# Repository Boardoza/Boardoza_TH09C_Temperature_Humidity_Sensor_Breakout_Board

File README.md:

# Boardoza TH09C Temperature Humidity Sensor Breakout Board
The TH09C Digital Temperature and Humidity Sensor Breakout Board offers reliable environmental monitoring with high accuracy and low power consumption. Featuring the TH09C sensor, this board provides precise digital temperature and humidity readings via an I<sup>2</sup>C interface. Its fast response time and high repeatability make it ideal for use in HVAC systems, weather stations, and other applications where environmental data is critical. 

### [Click here to purchase!](https://www.ozdisan.com/maker-and-iot-products/boardoza/boardoza-modules/BOARDOZA-TH09C/1206510)

|Front Side|Back Side|
|:---:|:---:|
| | |

---
## Key Features
- Ultra-Accurate Sensing: Temperature sensor with ±0.15°C accuracy and relative humidity sensor with typical ±2.0%RH accuracy.
- Wide Sensing Range: Supports temperature measurement from –40°C to 100°C and humidity from 0% to 100%.
- Digital Output: Provides digital temperature and humidity readings via TTL I2C interface for easy integration.
- Low Power Consumption: Optimized for battery-operated devices with minimal energy usage.
-Compact Design: Small form factor suitable for a wide range of environmental monitoring applications.

---

## Technical Specifications

**Input Voltage:**	2V - 5.5V

**Voltage Input Type:**	Molex 4 pin 2.50mm header

**Interface:** I<sup>2</sup>C  

**Functions:**	Temprature and Humidity Sensor

**Temperature Accuracy:** ±0.15°C  

**Humidity Accuracy:** Typical ±2.0% RH  

**Measurement Range:**	 -40°C ~ +100°C

**Operating Humidity:** 0% to 100% RH  

**Operating Temperature:**	-40°C ~ +100°C

**Board Dimensions:**	20mm x 20mm

---
## Board Pinout
| (J1) Pin Number | Pin Name | Description |
|:---:|:---:| --- |
| 1 | VCC | Power Supply |
| 2 | SCL | I<sup>2</sup>C Serial Clock Pin |
| 3 | SDA | I<sup>2</sup>C Serial Data Pin|
| 4 | GND | Ground|

---
## Board Dimensions

---
## Step Files

[Boardoza TH09C.step]( ./assets/TH09C%20Step.step)

---
## Datasheet

[Boardoza TH09C Datasheet.pdf](./assets/TH09C%20Datasheet.pdf)

---
## Version History
- V1.0.0 - Initial Release

---
## Support
- If you have any questions or need support, please contact support@boardoza.com

---
## License

Shield: [![CC BY-SA 4.0][cc-by-sa-shield]][cc-by-sa]

This work is licensed under a [Creative Commons Attribution-ShareAlike 4.0 International License][cc-by-sa].

[![CC BY-SA 4.0][cc-by-sa-image]][cc-by-sa]

[cc-by-sa]: http://creativecommons.org/licenses/by-sa/4.0/
[cc-by-sa-image]: https://licensebuttons.net/l/by-sa/4.0/88x31.png
[cc-by-sa-shield]: https://img.shields.io/badge/License-CC%20BY--SA%204.0-lightgrey.svg

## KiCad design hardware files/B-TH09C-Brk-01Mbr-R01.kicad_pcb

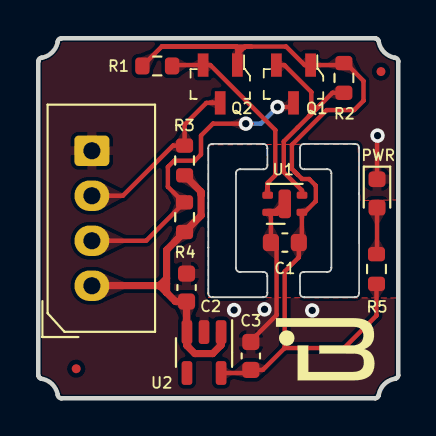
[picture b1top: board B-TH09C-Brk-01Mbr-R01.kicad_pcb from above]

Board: 2 copper layers, 20.0 x 20.0 mm, 14 parts (0 on the bottom side), 8 nets.

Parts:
C1: 100nF; C_0603_1608Metric
C2, C3: 1uF; C_0603_1608Metric
J1: MOLEX_CONNECTOR_1X4; 2317-04S_1x04_P2.50mm_Vertical
PWR: LED POWER; LED_0603_1608Metric
Q1, Q2: 2N7002_R1_00001; SOT-23-3
R1, R2, R3, R4, R5: 10K; R_0603_1608Metric
U1: TH09C
U2: TLV73333PDBVR; SOT-23-5

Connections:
+3V3: C1.1, C3.1, Q1.1 (G), Q2.1 (G), R1.1, R2.1, R5.1, U1.1 (VDD), U2.5 (OUT)
GND: C1.2, C2.2, C3.2, J1.4, PWR.1 (K), U1.4 (VSS), U1.5 (NC), U2.2 (GND)
unnamed: PWR.2 (A), R5.2
unnamed: Q1.2 (S), R2.2, U1.2 (SCL)
unnamed: Q2.2 (S), R1.2, U1.3 (SDA)
SCL: J1.2, Q1.3 (D), R4.2
SDA: J1.3, Q2.3 (D), R3.2
VCC: C2.1, J1.1, R3.1, R4.1, U2.1 (IN), U2.3 (EN)

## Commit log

2024-08-29 Initial commit for TH09C breakout board.
2024-12-26 Add Gerber files and update README for TH09C breakout board
2025-03-24 Add TH09C library
2025-03-24 Add url to library properties
2025-03-24 add paragraph to library properties
2025-03-24 add correct url to library properties
